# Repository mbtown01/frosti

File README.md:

# FROSTI

FROSTI (the Financially Responsive Open-Source Thermostat Initiative) is a
Raspberry Pi-based thermostat that monitors the current price of power on
the electric grid and changes temperature targets to minimize power usage 
during periods of high prices.

## Features

* Real-time monitoring of local power-price
* Web-based configuration
* 2.9" e-paper display clearly visible from a distance
* LED indicators for mode changes
* Full RESTful API for monitoring status and controlling from remote

## Links

[FROSTI main site](https://mbtown01.github.io/frosti/)

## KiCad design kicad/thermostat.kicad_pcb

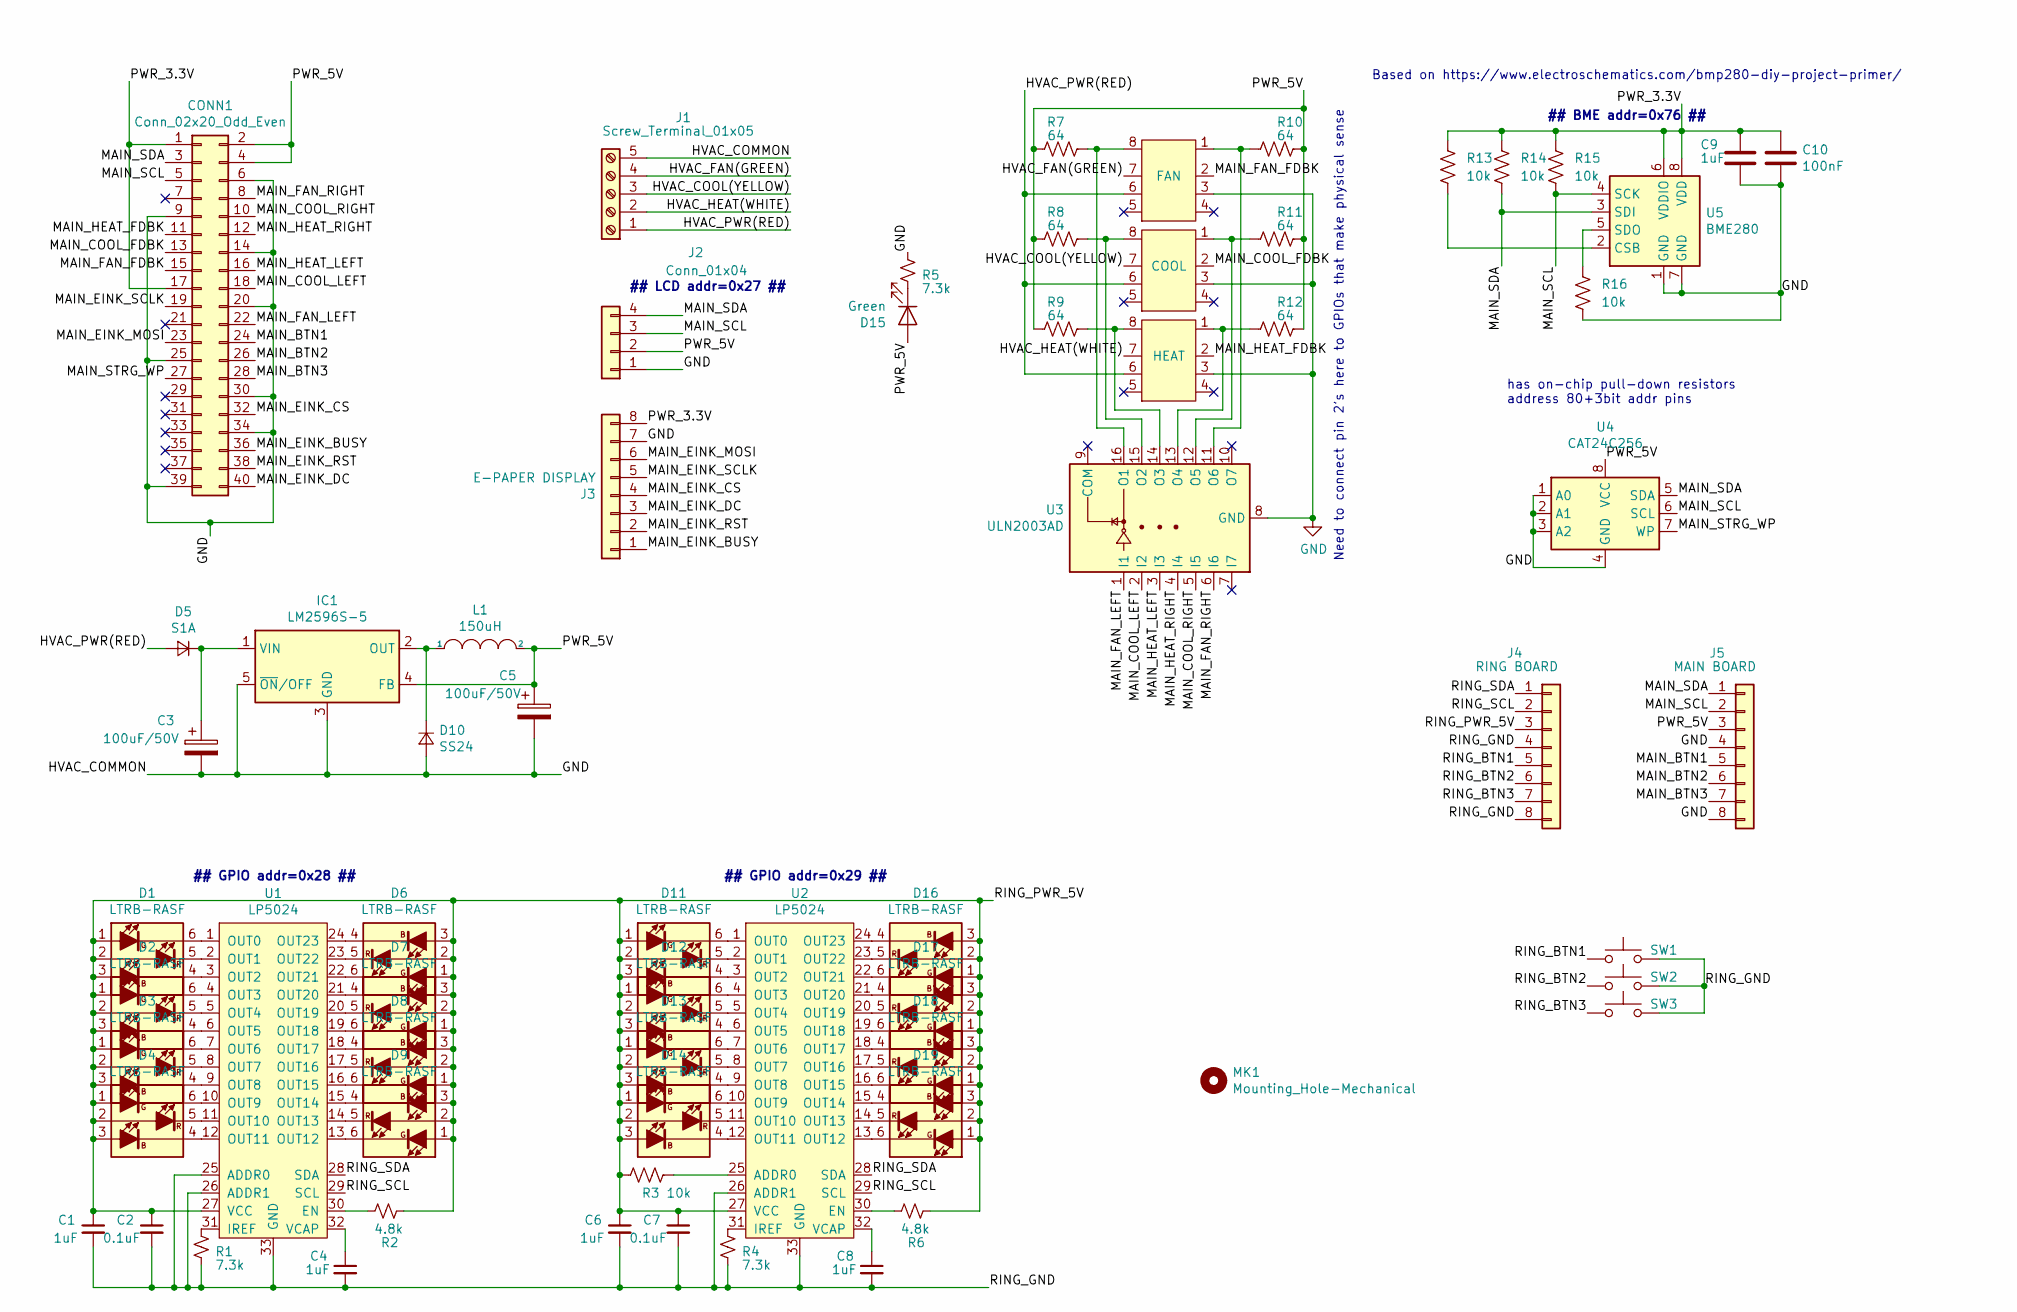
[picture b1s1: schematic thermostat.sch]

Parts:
C1, C4, C6, C8: 1uF; C_0805_2012Metric; Mouser 80-C0805C105M8RAUTO
C2, C7: 0.1uF; C_0805_2012Metric; Mouser 80-C0805X104K5R3316
C3, C5: 100uF/50V; C_Elec_8x10.2; MPN 667-EEE-FP1H101AV; Mouser 667-EEE-FP1H101AV
C9: 1uF; C_0805_2012Metric; MPN 80-C0805C105M8RAUTO; Mouser 80-C0805C105M8RAUTO
C10: 100nF; C_0805_2012Metric; MPN 80-C0805X104K5R3316; Mouser 80-C0805X104K5R3316
CONN1: Conn_02x20_Odd_Even; PinSocket_2x20_P2.54mm_Vertical; MPN 485-2243; Mouser 485-2243
D1, D2, D3, D4, D6, D7, D8, D9, D11, D12, D13, D14, D16, D17, D18, D19: LTRB-RASF; SOT-23-6; Mouser 720-LTRBRASFA7231
D5: S1A; D_SOD-123F; MPN 512-US1AFA; Mouser 512-US1AFA
D10: SS24; D_SMB; MPN 625-SS24-E3; Mouser 625-SS24-E3
D15: Green; LED_0805_2012Metric; MPN 710-150080GS75000; Mouser 710-150080GS75000
IC1: LM2596S-5; TO-263-5_TabPin3; MPN 926-LM2596S-5.0/NOPB; Mouser 926-LM2596S-5.0/NOPB
J1: Screw_Terminal_01x05; CUI_TB004-508-05BE; MPN 490-TB004-508-05BE; Mouser 490-TB004-508-05BE
J2: Conn_01x04; PinHeader_1x04_P2.54mm_Vertical
J3: E-PAPER DISPLAY; PinHeader_1x08_P2.54mm_Vertical
J4: RING BOARD; PinHeader_1x08_P2.54mm_Vertical
J5: MAIN BOARD; PinHeader_1x08_P2.54mm_Vertical
L1: 150uH; L_Wuerth_WE-PD-Typ-M-Typ-S; MPN 710-7447773151; Mouser 710-7447773151
MK1: Mounting_Hole-Mechanical; oshw-logo-8_silkscreen-front_8mm
R1, R4, R5: 7.3k; R_0805_2012Metric; Mouser 667-ERJ-PB6B7321V
R2, R6: 4.8k; R_0805_2012Metric; Mouser 667-ERJ-PB3B4751V
R3, R13, R14, R15, R16: 10k; R_0805_2012Metric; MPN 667-ERJ-PB6B1002V; Mouser 667-ERJ-PB6B1002V
R7, R8, R9, R10, R11, R12: 64; R_0805_2012Metric; MPN 667-ERJ-P06F64R9V; Mouser 667-ERJ-P06F64R9V
RELAY1: FAN; AGQ210A03; MPN 769-AGQ210A03Z; Mouser 769-AGQ210A03Z
RELAY2: COOL; AGQ210A03; MPN 769-AGQ210A03Z; Mouser 769-AGQ210A03Z
RELAY3: HEAT; AGQ210A03; MPN 769-AGQ210A03Z; Mouser 769-AGQ210A03Z
SW1, SW2, SW3: Button; SW_SPST_EVPBF; MPN 667-EVP-BFAC1A000; Mouser 667-EVP-BFAC1A000
U1, U2: LP5024; QFN-32-1EP_4x4mm_P0.4mm_EP2.9x2.9mm; Mouser 595-LP5024RSMR
U3: ULN2003AD; SOIC-16_3.9x9.9mm_P1.27mm; Mouser 595-ULN2003AD
U4: CAT24C256; SOIC-8-1EP_3.9x4.9mm_P1.27mm_EP2.29x3mm; Mouser 698-CAT24C256WI-GT3
U5: BME280; Bosch_LGA-8_2.5x2.5mm_P0.65mm_ClockwisePinNumbering; MPN 262-BME280; Mouser 262-BME280

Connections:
/HVAC_COOL(YELLOW): J1.3, RELAY2.7
/HVAC_FAN(GREEN): J1.4, RELAY1.7
/HVAC_HEAT(WHITE): J1.2, RELAY3.7
/HVAC_PWR(RED): D5.2 (A), J1.1, RELAY1.6, RELAY2.6, RELAY3.6
/MAIN_BTN1: CONN1.24, J5.5
/MAIN_BTN2: CONN1.26, J5.6
/MAIN_BTN3: CONN1.28, J5.7
/MAIN_COOL_FDBK: CONN1.13, RELAY2.2
/MAIN_COOL_LEFT: CONN1.18, U3.2 (I2)
/MAIN_COOL_RIGHT: CONN1.10, U3.5 (I5)
/MAIN_EINK_BUSY: CONN1.36, J3.1
/MAIN_EINK_CS: CONN1.32, J3.4
/MAIN_EINK_DC: CONN1.40, J3.3
/MAIN_EINK_MOSI: CONN1.23, J3.6
/MAIN_EINK_RST: CONN1.38, J3.2
/MAIN_EINK_SCLK: CONN1.19, J3.5
/MAIN_FAN_FDBK: CONN1.15, RELAY1.2
/MAIN_FAN_LEFT: CONN1.22, U3.1 (I1)
/MAIN_FAN_RIGHT: CONN1.8, U3.6 (I6)
/MAIN_HEAT_FDBK: CONN1.11, RELAY3.2
/MAIN_HEAT_LEFT: CONN1.16, U3.3 (I3)
/MAIN_HEAT_RIGHT: CONN1.12, U3.4 (I4)
/MAIN_SCL: CONN1.5, J2.3, J5.2, R15.2, U4.6 (SCL), U5.4 (SCK)
/MAIN_SDA: CONN1.3, J2.4, J5.1, R14.2, U4.5 (SDA), U5.3 (SDI)
/MAIN_STRG_WP: CONN1.27, U4.7 (WP)
/PWR_3.3V: C9.1, C10.1, CONN1.1, CONN1.17, J3.8, R13.1, R14.1, R15.1, U5.6 (VDDIO), U5.8 (VDD)
/PWR_5V: C5.1, CONN1.2, CONN1.4, D15.2 (A), IC1.4 (FB), J2.2, J5.3, L1.2, R7.1, R8.1, R9.1, R10.2, R11.2, R12.2, U4.8 (VCC)
/RING_BTN1: J4.5, SW1.1
/RING_BTN2: J4.6, SW2.1
/RING_BTN3: J4.7, SW3.1
/RING_GND: C1.2, C2.2, C4.2, C6.2, C7.2, C8.2, J4.4, J4.8, R1.2, R4.2, SW1.2, SW2.2, SW3.2, U1.25 (ADDR0), U1.26 (ADDR1), U1.33 (GND), U2.26 (ADDR1), U2.33 (GND)
/RING_PWR_5V: C1.1, C2.1, C6.1, C7.1, D1.1 (AG), D1.2 (AR), D1.3 (AB), D2.1 (AG), D2.2 (AR), D2.3 (AB), D3.1 (AG), D3.2 (AR), D3.3 (AB), D4.1 (AG), D4.2 (AR), D4.3 (AB), D6.1 (AG), D6.2 (AR), D6.3 (AB), D7.1 (AG), D7.2 (AR), D7.3 (AB), D8.1 (AG), D8.2 (AR), D8.3 (AB), D9.1 (AG), D9.2 (AR), D9.3 (AB), D11.1 (AG), D11.2 (AR), D11.3 (AB), D12.1 (AG), D12.2 (AR), D12.3 (AB), D13.1 (AG), D13.2 (AR), D13.3 (AB), D14.1 (AG), D14.2 (AR), D14.3 (AB), D16.1 (AG), D16.2 (AR), D16.3 (AB), D17.1 (AG), D17.2 (AR), D17.3 (AB), D18.1 (AG), D18.2 (AR), D18.3 (AB), D19.1 (AG), D19.2 (AR), D19.3 (AB), J4.3, R2.2, R3.1, R6.2, U1.27 (VCC), U2.27 (VCC)
/RING_SCL: J4.2, U1.29 (SCL), U2.29 (SCL)
/RING_SDA: J4.1, U1.28 (SDA), U2.28 (SDA)
GND: C3.2, C5.2, C9.2, C10.2, CONN1.6, CONN1.9, CONN1.14, CONN1.20, CONN1.25, CONN1.30, CONN1.34, CONN1.39, D10.2 (A), IC1.3 (GND), IC1.5 (~ON~/OFF), J1.5, J2.1, J3.7, J5.4, J5.8, R5.1, R16.2, RELAY1.3, RELAY2.3, RELAY3.3, U3.8 (GND), U4.1 (A0), U4.2 (A1), U4.3 (A2), U4.4 (GND), U5.1 (GND), U5.7 (GND)
unnamed: C3.1, D5.1 (K), IC1.1 (VIN)
unnamed: C4.1, U1.32 (VCAP)
unnamed: C8.1, U2.32 (VCAP)
unnamed: D1.4 (KB), U1.3 (OUT2)
unnamed: D1.5 (KR), U1.2 (OUT1)
unnamed: D1.6 (KG), U1.1 (OUT0)
unnamed: D2.4 (KB), U1.6 (OUT5)
unnamed: D2.5 (KR), U1.5 (OUT4)
unnamed: D2.6 (KG), U1.4 (OUT3)
unnamed: D3.4 (KB), U1.9 (OUT8)
unnamed: D3.5 (KR), U1.8 (OUT7)
unnamed: D3.6 (KG), U1.7 (OUT6)
unnamed: D4.4 (KB), U1.12 (OUT11)
unnamed: D4.5 (KR), U1.11 (OUT10)
unnamed: D4.6 (KG), U1.10 (OUT9)
unnamed: D6.4 (KB), U1.24 (OUT23)
unnamed: D6.5 (KR), U1.23 (OUT22)
unnamed: D6.6 (KG), U1.22 (OUT21)
unnamed: D7.4 (KB), U1.21 (OUT20)
unnamed: D7.5 (KR), U1.20 (OUT19)
unnamed: D7.6 (KG), U1.19 (OUT18)
unnamed: D8.4 (KB), U1.18 (OUT17)
unnamed: D8.5 (KR), U1.17 (OUT16)
unnamed: D8.6 (KG), U1.16 (OUT15)
unnamed: D9.4 (KB), U1.15 (OUT14)
unnamed: D9.5 (KR), U1.14 (OUT13)
unnamed: D9.6 (KG), U1.13 (OUT12)
unnamed: D10.1 (K), IC1.2 (OUT), L1.1
unnamed: D11.4 (KB), U2.3 (OUT2)
unnamed: D11.5 (KR), U2.2 (OUT1)
unnamed: D11.6 (KG), U2.1 (OUT0)
unnamed: D12.4 (KB), U2.6 (OUT5)
unnamed: D12.5 (KR), U2.5 (OUT4)
unnamed: D12.6 (KG), U2.4 (OUT3)
unnamed: D13.4 (KB), U2.9 (OUT8)
unnamed: D13.5 (KR), U2.8 (OUT7)
unnamed: D13.6 (KG), U2.7 (OUT6)
unnamed: D14.4 (KB), U2.12 (OUT11)
unnamed: D14.5 (KR), U2.11 (OUT10)
unnamed: D14.6 (KG), U2.10 (OUT9)
unnamed: D15.1 (K), R5.2
unnamed: D16.4 (KB), U2.24 (OUT23)
unnamed: D16.5 (KR), U2.23 (OUT22)
unnamed: D16.6 (KG), U2.22 (OUT21)
unnamed: D17.4 (KB), U2.21 (OUT20)
unnamed: D17.5 (KR), U2.20 (OUT19)
unnamed: D17.6 (KG), U2.19 (OUT18)
unnamed: D18.4 (KB), U2.18 (OUT17)
unnamed: D18.5 (KR), U2.17 (OUT16)
unnamed: D18.6 (KG), U2.16 (OUT15)
unnamed: D19.4 (KB), U2.15 (OUT14)
unnamed: D19.5 (KR), U2.14 (OUT13)
unnamed: D19.6 (KG), U2.13 (OUT12)
unnamed: R1.1, U1.31 (IREF)
unnamed: R2.1, U1.30 (EN)
unnamed: R3.2, U2.25 (ADDR0)
unnamed: R4.1, U2.31 (IREF)
unnamed: R6.1, U2.30 (EN)
unnamed: R7.2, RELAY1.8, U3.16 (O1)
unnamed: R8.2, RELAY2.8, U3.15 (O2)
unnamed: R9.2, RELAY3.8, U3.14 (O3)
unnamed: R10.1, RELAY1.1, U3.11 (O6)
unnamed: R11.1, RELAY2.1, U3.12 (O5)
unnamed: R12.1, RELAY3.1, U3.13 (O4)
unnamed: R13.2, U5.2 (CSB)
unnamed: R16.1, U5.5 (SDO)

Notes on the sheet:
Based on https://www.electroschematics.com/bmp280-diy-project-primer/
## LCD addr=0x27 ##
## BME addr=0x76 ##
Need to connect pin 2’s here to GPIOs that make physical sense
## GPIO addr=0x28 ##
## GPIO addr=0x29 ##
has on-chip pull-down resistors address 80+3bit addr pins

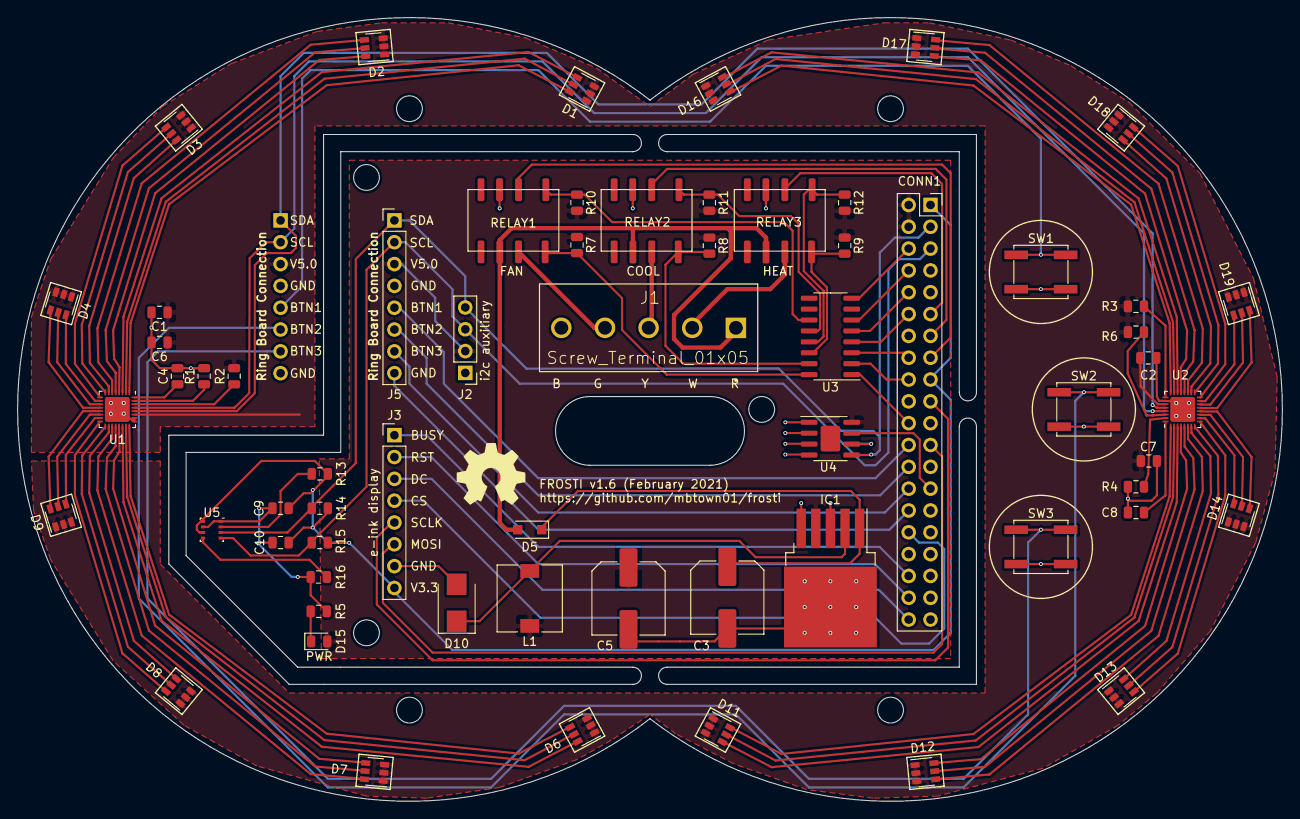
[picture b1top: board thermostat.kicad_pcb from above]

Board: 2 copper layers, 147.2 x 91.2 mm, 65 parts (1 on the bottom side), 101 nets.

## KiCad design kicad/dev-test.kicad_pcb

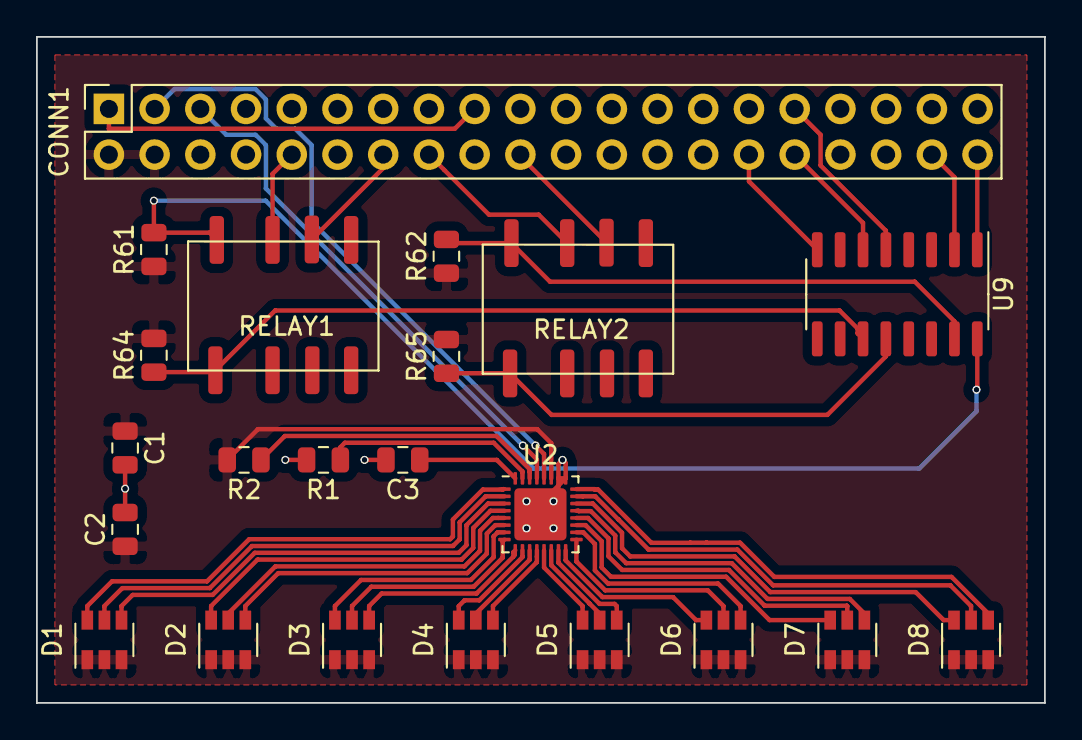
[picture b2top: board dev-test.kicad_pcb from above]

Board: 2 copper layers, 56.0 x 37.0 mm, 22 parts (0 on the bottom side), 42 nets.

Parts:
C1, C3: 1uF; C_0805_2012Metric
C2: 0.1uF; C_0805_2012Metric
CONN1: Conn_02x20_Odd_Even; PinSocket_2x20_P2.54mm_Vertical
D1, D2, D3, D4, D5, D6, D7, D8: LTRB-RASF; SOT-23-6
R1: 7.3k; R_0805_2012Metric
R2: 4.8k; R_0805_2012Metric
R61, R62, R64, R65: 64; R_0805_2012Metric
RELAY1: FAN; AGQ210A03
RELAY2: HEAT; AGQ210A03
U2: LP5024; QFN-32-1EP_4x4mm_P0.4mm_EP2.9x2.9mm
U9: ULN2003AD; SOIC-16_3.9x9.9mm_P1.27mm

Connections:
/GPIO2(SDA1): CONN1.3, U2.28
/GPIO3(SCL1): CONN1.5, U2.29
/GPIO6: CONN1.31, U9.5
/GPIO12(PWM0): CONN1.32, U9.6
/GPIO15(RXD0): CONN1.10, RELAY1.7
/GPIO20(SPI1_MOSI): CONN1.38, U9.2
/GPIO21(SPI1_SCK): CONN1.40, U9.1
/GPIO23(GEN4): CONN1.16, RELAY2.7
/PWR_3.3V: CONN1.1, CONN1.17
/PWR_5V: C1.1, C2.1, CONN1.2, CONN1.4, D1.1, D1.2, D1.3, D2.1, D2.2, D2.3, D3.1, D3.2, D3.3, D4.1, D4.2, D4.3, D5.1, D5.2, D5.3, D6.1, D6.2, D6.3, D7.1, D7.2, D7.3, D8.1, D8.2, D8.3, R2.2, R61.1, R62.1, R64.2, R65.2, U2.27
GND: C1.2, C2.2, C3.2, CONN1.6, CONN1.9, CONN1.14, CONN1.20, CONN1.25, CONN1.30, CONN1.34, CONN1.39, R1.2, RELAY1.6, RELAY2.6, U2.25, U2.26, U2.33, U9.8
unnamed: C3.1, U2.32
unnamed: D1.4, U2.3
unnamed: D1.5, U2.2
unnamed: D1.6, U2.1
unnamed: D2.4, U2.6
unnamed: D2.5, U2.5
unnamed: D2.6, U2.4
unnamed: D3.4, U2.9
unnamed: D3.5, U2.8
unnamed: D3.6, U2.7
unnamed: D4.4, U2.12
unnamed: D4.5, U2.11
unnamed: D4.6, U2.10
unnamed: D5.4, U2.15
unnamed: D5.5, U2.14
unnamed: D5.6, U2.13
unnamed: D6.4, U2.18
unnamed: D6.5, U2.17
unnamed: D6.6, U2.16
unnamed: D7.4, U2.21
unnamed: D7.5, U2.20
unnamed: D7.6, U2.19
unnamed: D8.4, U2.24
unnamed: D8.5, U2.23
unnamed: D8.6, U2.22
unnamed: R1.1, U2.31
unnamed: R2.1, U2.30
unnamed: R61.2, RELAY1.8, U9.16
unnamed: R62.2, RELAY2.8, U9.15
unnamed: R64.1, RELAY1.1, U9.11
unnamed: R65.1, RELAY2.1, U9.12

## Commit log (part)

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2019-07-03 Restructure, add Flask support
2019-07-05 Better integration; simplify Flask; interfaces
2019-07-05 Clean more pep8 warnings
2019-07-06 Clean up names
2019-07-07 move API calls to class members
2019-07-08 started making modules but not perfect
2019-07-08 refactor events
2019-07-13 Updates to support non-Mac dev clients
2019-07-13 Integrate code coverage, add thermostat logic
2019-07-15 first pass at LCD, not working
2019-07-20 Generic hardware but no tests yet
2019-07-21 First working simple LCD temp display
2019-07-23 updates to hardware
2019-07-26 blocking dumb terminal working
2019-07-26 remove file
2019-07-28 Reasonably working terminal
2019-07-31 updates/clean-up
2019-07-31 refactor settings to singleton
2019-08-03 more working javascript changes
2019-08-17 add griddy query tool
2019-08-18 some board changes, probably too small...
2019-08-21 First take at the bigger board
2019-08-26 Almost ready for ethernet header
2019-08-28 Ready for checkout and routing
2019-08-31 more updates, backstop before 24v conversation
2019-09-01 ready for pours and routing
2019-09-02 Larger power traces, ready for clean-up
2019-09-02 more cleaning
2019-09-02 remove backups
2019-09-02 BOM updated and SUBMITTED!!!
2019-09-07 add config; clean-up griddy query script
2019-09-10 convert api from a singleton
2019-09-12 Fix config file
2019-09-19 updates to stage for travel
2019-09-20 GoGriddy integrated, still needs configured
2019-09-22 completely refactor thermostat
2019-09-25 clean up config
2019-09-29 Working price checking
2019-09-29 First deployment to 3rd floor
2019-09-30 better settings tests
2019-10-01 fix thermostat startup to _defaults issue
2019-10-04 working 2nd rpi for teting
2019-10-05 Refactor to event-based, still need to fix rpi
2019-10-05 all event driven, after lots of work
2019-10-06 more bug fixes in thermostat logic
2019-10-06 update ip address of dev machine
2019-10-08 incomplete fixes
2019-10-10 more tests and thermostat logic cleanup
2019-10-11 even more fixed tests
2019-10-11 convert config to service
2019-10-11 rename EventHandler
2019-10-13 more test cleanup, resolve time on eventbus
2019-10-16 updates to web api
2019-10-19 remove design doc
2019-11-17 updates to documentation
2019-11-25 docker compose updates
2019-11-27 cleaned compose file
2019-12-02 Resolves #6
2019-12-15 Should fix #4
2019-12-15 Track relay toggled for ALL changes of the relay
2019-12-19 simple updates
2019-12-19 upates
2019-12-25 debug start containers; restore last targets
2019-12-28 some spice adds
2019-12-29 changes/updates
2020-01-01 addition of bmp280
2020-01-02 new symbol for transistor
2020-01-03 Updated ALL references to new library
2020-01-04 ltc4041 overall design ready
2020-01-06 almost routed
2020-01-06 fully routed v2.0
2020-01-10 updates, close to thermostat v2.1
2020-01-10 passing v2.0 to MacroFab
2020-01-27 add some freecad work
2020-02-16 sync changes
2020-02-19 more updates
2020-02-22 almost ready to route
2020-02-23 Routing complete
2020-02-23 change of silkscreen to reflect v3.0
2020-03-01 cleaner gitignore for kicad
2020-03-01 refactor api into single class service
2020-03-03 refactor services and events
2020-03-06 now supporting dev containers via vscode
2020-03-07 cleanup
2020-03-08 cleaning up container creation
2020-03-08 resolves #7
2020-03-21 updates, cad broken
2020-03-25 updates to docker file to use python 3.7
2020-03-27 Updates to the docker config, tested w/ VSCode
2020-03-28 docker updates
2020-03-28 update gitignore
2020-03-29 Re-route 23017
2020-04-04 routed board
2020-04-04 moved some diagram objects around
2020-04-07 build against raspbian, not tested
2020-04-08 more fixes for docker on RPi
2020-04-18 fix dev flags
2020-04-19 clean terminal display, add instructions
2020-04-20 initial led implementation; fix for EventBus loop
2020-04-22 move testing to the raspberry pi
2020-04-23 container fixes for raspberrypi
2020-04-23 refactor
2020-04-24 cleanup, refactor user interface
2020-04-25 refactor imports, fix unit tests
2020-04-26 more refactoring, update relay in schematic
2020-04-28 updates to work with hardware v1
2020-04-28 add import
2020-04-29 more fixes
2020-05-01 more docker-compose cleanup
2020-05-01 fix v1 hardware
2020-05-06 some grafana updates to show min/max
2020-05-09 add diagnostics
2020-05-10 add i2c to ansible
2020-05-10 add timezone config, default to Central time
2020-05-15 major updates to grafana, postgres
2020-05-15 more queries
2020-05-16 move grafana to custom image
2020-05-16 fix wrong grafana image for pi, add --arch
2020-05-17 big docker refactor
2020-05-21 fix comfort min/max area fill
2020-05-23 actual working setup...
2020-05-25 1st working version of simple control panel
2020-05-28 new relay driver circuitry, layout needed
2020-05-28 resolves #12
2020-06-17 moving towards new schema
2020-07-01 minor clean-up
2020-07-06 the big SettingsService refactor
2020-07-26 add safeInvoke, fix some tests
2020-07-26 docker work, merging
2020-07-26 add dist; more actions
2020-07-26 another shot at qemu
2020-07-26 even better
2020-07-26 fix arm compose file
2020-07-26 stop bringing in source
2020-07-26 debug arm builds
2020-07-27 fix dockerfile
2020-07-28 add support for timezones
2020-08-02 mostly working first pass at configuration panel
2020-08-21 much cleaner api testing
2020-10-19 some progress w/ vue
2020-11-15 progress toward new design
2020-11-25 completely routed board
2020-11-25 add pages
2020-11-25 remove pages
2020-11-28 add index file
2020-11-28 Set theme jekyll-theme-architect
2020-11-29 Set theme jekyll-theme-minimal
2020-11-29 more jekyll
2020-11-29 full re-name to frosti
2020-12-13 blog post
2020-12-22 some display progress
2020-12-24 more display progress
2020-12-28 cleaner led ring threading
2020-12-29 add requirements
2020-12-30 installer work
2020-12-31 first working image builder
2020-12-31 add docker-compose installation
2021-01-02 almost full boot!
2021-01-03 almost there w/ setup
2021-01-03 working base imager (finally)
2021-01-06 breadcrumbs on wifi setup
2021-01-11 more config work
2021-01-15 cleaned up v1.6 board
2021-01-18 image builder worked all the way through!
2021-01-18 fix for exception on chart draw
2021-01-31 hardware abstraction
    Making way for a first test of hardware v6
2021-02-13 add watchdog
2021-03-30 Bump kramdown from 2.3.0 to 2.3.1 in /docs
    Bumps [kramdown](https://github.com/gettalong/kramdown) from 2.3.0 to 2.3.1.
    - [Release notes](https://github.com/gettalong/kramdown/releases)
    - [Changelog](https://github.com/gettalong/kramdown/blob/master/doc/news.page)
    - [Commits](https://github.com/gettalong/kramdown/commits)
2021-04-20 Bump ssri from 6.0.1 to 6.0.2 in /client
    Bumps [ssri](https://github.com/npm/ssri) from 6.0.1 to 6.0.2.
    - [Release notes](https://github.com/npm/ssri/releases)
    - [Changelog](https://github.com/npm/ssri/blob/v6.0.2/CHANGELOG.md)
    - [Commits](https://github.com/npm/ssri/compare/v6.0.1...v6.0.2)
2021-05-10 Bump url-parse from 1.4.7 to 1.5.1 in /client
    Bumps [url-parse](https://github.com/unshiftio/url-parse) from 1.4.7 to 1.5.1.
    - [Release notes](https://github.com/unshiftio/url-parse/releases)
    - [Commits](https://github.com/unshiftio/url-parse/compare/1.4.7...1.5.1)
2021-05-11 Bump lodash from 4.17.20 to 4.17.21 in /client
    Bumps [lodash](https://github.com/lodash/lodash) from 4.17.20 to 4.17.21.
    - [Release notes](https://github.com/lodash/lodash/releases)
    - [Commits](https://github.com/lodash/lodash/compare/4.17.20...4.17.21)
2021-05-29 Bump dns-packet from 1.3.1 to 1.3.4 in /client
    Bumps [dns-packet](https://github.com/mafintosh/dns-packet) from 1.3.1 to 1.3.4.
    - [Release notes](https://github.com/mafintosh/dns-packet/releases)
    - [Changelog](https://github.com/mafintosh/dns-packet/blob/master/CHANGELOG.md)
    - [Commits](https://github.com/mafintosh/dns-packet/compare/v1.3.1...v1.3.4)
2021-06-06 Bump ws from 6.2.1 to 6.2.2 in /client
    Bumps [ws](https://github.com/websockets/ws) from 6.2.1 to 6.2.2.
    - [Release notes](https://github.com/websockets/ws/releases)
    - [Commits](https://github.com/websockets/ws/commits)
    ---
    updated-dependencies:
    - dependency-name: ws
2021-07-13 Bump addressable from 2.7.0 to 2.8.0 in /docs
    Bumps [addressable](https://github.com/sporkmonger/addressable) from 2.7.0 to 2.8.0.
    - [Release notes](https://github.com/sporkmonger/addressable/releases)
    - [Changelog](https://github.com/sporkmonger/addressable/blob/main/CHANGELOG.md)
    - [Commits](https://github.com/sporkmonger/addressable/compare/addressable-2.7.0...addressable-2.8.0)
    ---
    updated-dependencies:
2021-10-06 Bump url-parse from 1.4.7 to 1.5.3 in /client
    Bumps [url-parse](https://github.com/unshiftio/url-parse) from 1.4.7 to 1.5.3.
    - [Release notes](https://github.com/unshiftio/url-parse/releases)
    - [Commits](https://github.com/unshiftio/url-parse/compare/1.4.7...1.5.3)
    ---
    updated-dependencies:
    - dependency-name: url-parse
2022-02-13 Bump follow-redirects from 1.13.0 to 1.14.8 in /client
    Bumps [follow-redirects](https://github.com/follow-redirects/follow-redirects) from 1.13.0 to 1.14.8.
    - [Release notes](https://github.com/follow-redirects/follow-redirects/releases)
    - [Commits](https://github.com/follow-redirects/follow-redirects/compare/v1.13.0...v1.14.8)
    ---
    updated-dependencies:
    - dependency-name: follow-redirects
2022-02-27 Bump url-parse from 1.4.7 to 1.5.10 in /client
    Bumps [url-parse](https://github.com/unshiftio/url-parse) from 1.4.7 to 1.5.10.
    - [Release notes](https://github.com/unshiftio/url-parse/releases)
    - [Commits](https://github.com/unshiftio/url-parse/compare/1.4.7...1.5.10)
    ---
    updated-dependencies:
    - dependency-name: url-parse
2022-04-29 Bump async from 2.6.3 to 2.6.4 in /client
    Bumps [async](https://github.com/caolan/async) from 2.6.3 to 2.6.4.
    - [Release notes](https://github.com/caolan/async/releases)
    - [Changelog](https://github.com/caolan/async/blob/v2.6.4/CHANGELOG.md)
    - [Commits](https://github.com/caolan/async/compare/v2.6.3...v2.6.4)
    ---
    updated-dependencies:
2022-06-23 Bump shell-quote from 1.7.2 to 1.7.3 in /client
    Bumps [shell-quote](https://github.com/substack/node-shell-quote) from 1.7.2 to 1.7.3.
    - [Release notes](https://github.com/substack/node-shell-quote/releases)
    - [Changelog](https://github.com/substack/node-shell-quote/blob/master/CHANGELOG.md)
    - [Commits](https://github.com/substack/node-shell-quote/compare/v1.7.2...1.7.3)
    ---
    updated-dependencies:
2022-07-21 Bump terser from 4.8.0 to 4.8.1 in /client
    Bumps [terser](https://github.com/terser/terser) from 4.8.0 to 4.8.1.
    - [Release notes](https://github.com/terser/terser/releases)
    - [Changelog](https://github.com/terser/terser/blob/master/CHANGELOG.md)
    - [Commits](https://github.com/terser/terser/commits)
    ---
    updated-dependencies:
2022-11-10 Bump minimatch from 3.0.4 to 3.1.2 in /client
    Bumps [minimatch](https://github.com/isaacs/minimatch) from 3.0.4 to 3.1.2.
    - [Release notes](https://github.com/isaacs/minimatch/releases)
    - [Commits](https://github.com/isaacs/minimatch/compare/v3.0.4...v3.1.2)
    ---
    updated-dependencies:
    - dependency-name: minimatch
2022-12-08 Bump qs from 6.5.2 to 6.5.3 in /client
    Bumps [qs](https://github.com/ljharb/qs) from 6.5.2 to 6.5.3.
    - [Release notes](https://github.com/ljharb/qs/releases)
    - [Changelog](https://github.com/ljharb/qs/blob/main/CHANGELOG.md)
    - [Commits](https://github.com/ljharb/qs/compare/v6.5.2...v6.5.3)
    ---
    updated-dependencies:
